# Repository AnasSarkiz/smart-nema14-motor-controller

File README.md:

# Active routing — 0.0.53-alpha.0

Read `docs/REV53-LOGIC-POWER-ESCAPES.md`. The canonical native replay retains
all56/120 complete nets, with240 required opens,128 tracks,82 ordinary0.30/0.45mm
full through vias,five manifested TypeVII thermal vias and seven filled regions.
Native other-errors:0; unchanged strict and filled-copper clearance failures:0;
GND remains one physical network. Original purchased definitions, all165 fitted
model transforms, capacitor placement, motor and carrier are preserved.
The complete USB_VDD bypass/return geometry is screened; V3V3 remains incomplete.
Continue3.3V/core power,PD/eFuse controls,USB pair and ALL remaining physical nets.
Publication is WIP; loaded power/USB/thermal,complete CAM,quote and hardware tests
remain pending. Do not stop at this step. PROTOTYPE FABRICATION READY:NO.

---

# Active routing — 0.0.52-alpha.0

Read `docs/REV52-VM-POWER-ROUTING.md`. Qualified power019 joins56/120 required
nets, including every RAW/protected-VBUS/VM terminal and all prior54 nets.
265 opens,112 tracks,79 ordinary0.30/0.45mm full through vias,five manifested
TypeVII thermal vias,eight native filled regions. Native other-errors:0; strict
and filled-copper clearance failures:0; GND remains one physical network.
Keep all supplier imports/models/placement unchanged. Continue3.3V and core
power,PD/eFuse controls,USB pair with return path,then ALL remaining connections.
Accepted main routes are phase0; VM fanouts phase2; new selected-net routing
is phase3 so existing power copper is a frozen obstacle. Publication is WIP;
loaded power/USB/thermal,complete CAM,assembly quote and hardware tests pending.
Do not stop at this checkpoint. PROTOTYPE FABRICATION READY:NO. No board order.

---

# Smart NEMA 14 Motor Controller

Revision **0.0.53-alpha.0 — WIP prototype** uses **RP2040** and **two USB-C ports**:
`J_USB` supplies motor power through STUSB4500 USB-PD; `J_DATA` connects the
computer's USB data. The board is 35 × 35 mm, four layers, with the original
STEPPERONLINE 14HM11-0404S motor and front carrier. Motor control is open loop.

Configure and read back STUSB4500 NVM for two active sink PDOs: 5 V bootstrap
and preferred 15 V / 1.5 A. Deactivate the factory 20 V PDO. The hardware
interlock combines the 15 V indication, live sink path, MCU request and logic
supervisor. Factory settings alone do not establish a 15 V motor contract.
Computer VBUS only supplies its presence-sense divider; computer power cannot
power the controller or motor. The POWER port must also be connected.

The checked copper connects **56/120 required nets**, including all raw/protected VBUS and all fifteen motor VM terminals: **128 traces, 82 ordinary
0.30 mm drill / 0.45 mm pad through vias, five filled/capped TMC2209 thermal
vias and seven native filled regions**. It has **240 open-port errors**, zero other
native errors and zero independent copper-clearance violations. Routing and
loaded power, USB, thermal and fresh manufacturing qualification continue.
**PROTOTYPE FABRICATION READY: NO. Not hardware tested.**

All 166 electronic references have purpose notes on eleven native A4 sheets;
165 are fitted (R50 is optional). Original official JLCPCB definitions and
OBJ/STEP models are preserved. Actual assembly, model registration and bounded
connector/cable checks pass. See [current routing evidence](docs/REV53-LOGIC-POWER-ESCAPES.md),
[two-port electrical review](docs/REV50-TWO-PORT-ROUTING.md),
[15 V NVM programming](docs/STUSB4500-15V-PROGRAMMING.md), [validation](VALIDATION.md)
and [Cloud task](docs/cloud/TASK.md). The remaining imported TVS schematic
rotation finding is disclosed. Exact-part stock checks are snapshots, not a
customer PCBA allocation or assembly quote.

The lockfile pins Bun 1.3.9, tscircuit 0.0.2757, CLI 0.1.2257, core 0.0.2107,
native Pipeline9 0.0.962 and coherent released dependencies.

```bash
bash scripts/cloud-setup.sh
bash scripts/cloud-smoke.sh
bun run typecheck
bun run build
```

Setup/startup do not route. The intermediate build exits 1 while required opens
remain. Routing uses bounded native Pipeline9 batches and qualified saved source
paths, without supplier edits, generated JSON edits or weaker checks.

Public destinations: [GitHub main](https://github.com/AnasSarkiz/smart-nema14-motor-controller)
and [tscircuit](https://tscircuit.com/AnasSarkiz/smart-nema14-motor-controller--01a0fd9b).
Publication receipts identify exact matching source, Circuit JSON and CAD bytes.
No fabrication order is authorized.

---

## Historical revision 48 record

The following is preserved history. Its one-port architecture, counts, toolchain
and CAD limitations do not describe the current two-port revision.

# Smart NEMA 14 Motor Controller

Revision **0.0.48-alpha.0** — **RP2040 + autonomous STUSB4500 USB-PD**.
**Partially routed prototype. PROTOTYPE FABRICATION READY: NO. Not hardware tested.**

The user-requested redesign replaces STM32/TCPP01 with official RP2040,
external 2 MB QSPI flash, 12 MHz crystal and a dedicated STUSB4500 sink with
back-to-back P-channel power switches. The former MCU had UCPD hardware but
qualified PD firmware was absent; USB-C alone did not establish working PD.
The new controller negotiates autonomously using its factory sink PDOs.
Firmware must qualify the actual contract before enabling the motor/current.

The CAN interface uses a new MCP2515 SPI controller and retains SN65HVD230.
A functional magnetic buzzer driver is added; TMP112 remains the I2C sensor.
Its sheet now includes the sensor, pull-ups, bypasses and buzzer circuit.
All **147 electronic references / 146 default fitted** have purpose notes on
nine native A4 sheets. Only R50, the optional CAN termination link, is DNP.

The board remains **35 x 35 mm, four layers**, with the original four
connectors, front carrier and exact **STEPPERONLINE 14HM11-0404S** single-front-
shaft motor. AS5600 stays removed; motor control is open loop.

See [the complete redesign and every review request](docs/RP2040-USB-PD-REDESIGN.md),
[current routing checkpoint](docs/REV48-ROUTING-CHECKPOINT.md),
[current validation](VALIDATION.md) and [Cloud task](docs/cloud/TASK.md).
Manufacturer pin/BOM and initial placement/model reviews permit routing.
Complete copper, power/USB/thermal/CAM qualification and hardware tests remain.
The full official schematic analyzer leaves one imported TVS rotation defect.
No purchased import, pad mapping, model, DRC or TypeScript rule is patched.

Fresh native [Circuit JSON](dist/index/circuit.json) contains **97 traces,
79 ordinary through vias and8 native ground pours**. **64 of108 required nets** have
one independently measured physical copper island. Native checking still
reports **227 open-port errors**, with zero other native errors and zero strict
copper/drill/edge/keepout violations in this partial build. The build exits1
because connectivity remains incomplete. It is not ready to order.
Old STM32 copper is preserved historically and deliberately cannot be replayed
against the new RP2040 pin selectors. Revision 43 Gerbers/exports cannot
manufacture this revision.

The reproducible lockfile uses Bun1.3.9, tscircuit0.0.2750 / CLI0.1.2254 /
core0.0.2105 / native Pipeline9 0.0.962 with coherent released dependencies.
Frozen installation succeeds through the official registry mirror with normal
TLS/integrity. No substitute router, dependency patch or proxy bypass is used.
Saving a Cloud draft alone does not activate its network policy.

All12 ICs and all146 fitted genuine STEP models pass actual CadQuery import,
solid validity and export/reimport. Current internal placements pass actual mounted146-mesh nominal envelope checks.
The native placement screen retains three orientation suggestions; they remain
explicit alongside the one imported TVS schematic-style finding.
All54 exact part numbers have positive official JLCPCB stock/SMT availability
checked2026-10-07 12:01UTC; customer allocation remains pending. The5-board
fitted-part baseline is$27.261 per board, excluding PCB, assembly/loading fees,
supplier losses, shipping/tax, carrier and motor. This is not a delivered quote.

```bash
bash scripts/cloud-setup.sh
bash scripts/cloud-smoke.sh
bun run build
bun run typecheck
```

Installation/startup do not route. Routing uses one bounded selected-net
native Pipeline9 job at a time on Linux through scripts/run-cloud-routing.py,
plus supported native saved manual paths. All56 current vias measure0.30mm
drill /0.45mm pad and span all four layers. Via-in-pad is disabled. Outer power,
complete loaded widths and USB coupling/return require copper qualification.

The standard JST programmer's five-pin order and protected SWD paths are
preserved. Its VOUT is isolated; independently power the target and use an
RP2040 programming target. The 38 wiring assertions pass; successful flashing
has not been tested.

Public destinations: [GitHub main](https://github.com/AnasSarkiz/smart-nema14-motor-controller)
and [tscircuit](https://tscircuit.com/AnasSarkiz/smart-nema14-motor-controller--01a0fd9b).
Publication receipts identify the exact successfully uploaded revision; a
local version number does not prove publication. The runtime packet includes
unchanged official OBJ/STEP dependencies and matching native JSON, excluding
old experiments. Full historical evidence and the tscircuit skill remain in Git.
No fabrication order is authorized.

The mounted native GLB has an empty J_SWD mesh after intermittent HTTP503
from the standard programmer's original model URL. The mechanical guard
reports145/146 fitted meshes measured, no carrier/fastener/pair collisions
among those145, and **fails** on the missing connector. A successful builder
exit does not qualify complete CAD rendering or fit. Original supplier models
and URLs are retained; no placeholder or changed component is substituted.

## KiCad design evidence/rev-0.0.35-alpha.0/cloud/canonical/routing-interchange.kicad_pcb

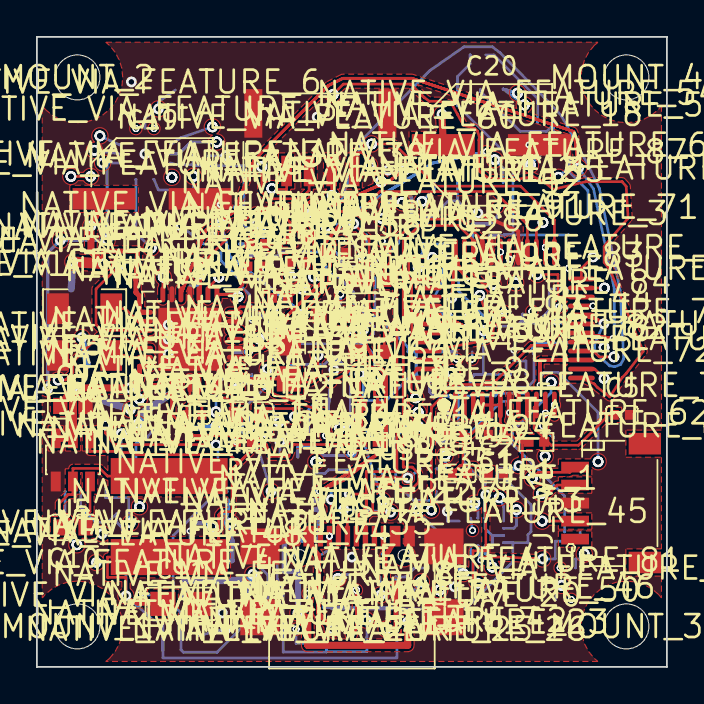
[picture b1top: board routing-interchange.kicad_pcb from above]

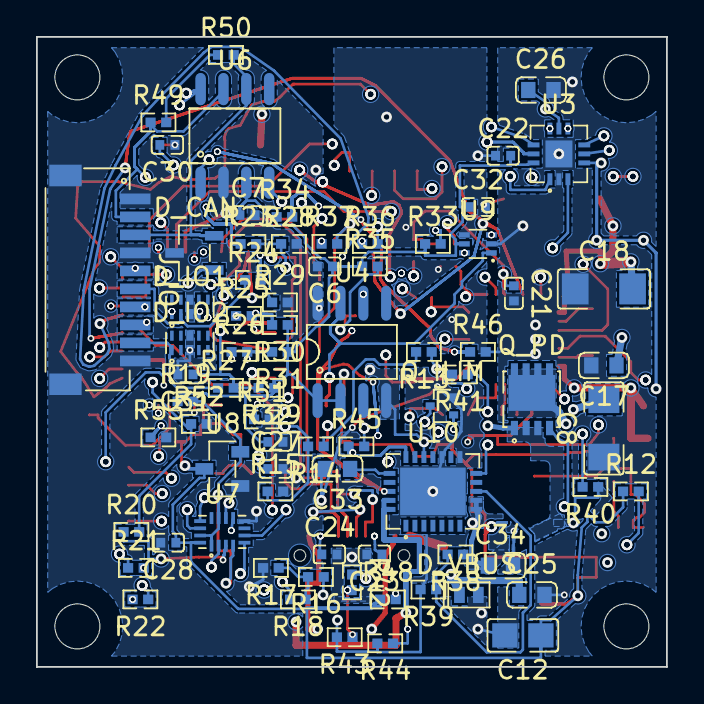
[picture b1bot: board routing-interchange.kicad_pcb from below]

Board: 4 copper layers, 35.0 x 35.0 mm, 213 parts (75 on the bottom side), 82 nets.

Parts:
C1: 100nF; C1
C2: 4.7uF; C2
C3: 100nF; C3
C4: 100nF; C4
C5: 100nF; C5
C6: 100nF; C6
C7: 100nF; C7
C8: 10uF; C8
C9: 100nF; C9
C10: 100nF; C10
C11: 22uF; C11
C12: 22uF; C12
C13: 22nF; C13
C14: 100nF; C14
C15: 4.7uF; C15
C16: 100nF; C16
C17: 100nF; C17
C18: 10uF; C18
C19: 100uF; C19
C20: 100uF; C20
C21: 100nF; C21
C22: 100nF; C22
C23: 330pF; C23
C24: 330pF; C24
C25: 2.2uF; C25
C26: 100nF; C26
C27: 100nF; C27
C28: 100nF; C28
C29: 100nF; C29
C30: 100nF; C30
C31: 100nF; C31
C32: 100nF; C32
C33: 2.2uF; C33
C34: 2.2uF; C34
D_CAN: SM712.TCT; D_CAN
D_IO1: TPD4E05U06DQAR; D_IO1
D_IO2: TPD4E05U06DQAR; D_IO2
D_USB: TPD2EUSB30ADRTR; D_USB
D_VBUS: ESDA25P35-1U1M; D_VBUS
J_IO: SM10B-SRSS-TB(LF)(SN); J_IO
J_MOTOR: SM04B-GHS-TB(LF)(SN); J_MOTOR
J_SWD: J_SWD
J_USB: USB4110-GF-A; J_USB
L1: 3.9µH; L1
LED_FAULT: XL-1608SYGC-06; LED_FAULT
LED_POWER: XL-1608SYGC-06; LED_POWER
LED_STATUS: XL-1608SYGC-06; LED_STATUS
MOUNT_1, MOUNT_2, MOUNT_3, MOUNT_4: hole_circle_holeDiameter2.5mm
NATIVE_VIA_FEATURE_1: NATIVE_VIA_FEATURE_1
NATIVE_VIA_FEATURE_2: NATIVE_VIA_FEATURE_2
NATIVE_VIA_FEATURE_3: NATIVE_VIA_FEATURE_3
NATIVE_VIA_FEATURE_4: NATIVE_VIA_FEATURE_4
NATIVE_VIA_FEATURE_5: NATIVE_VIA_FEATURE_5
NATIVE_VIA_FEATURE_6: NATIVE_VIA_FEATURE_6
NATIVE_VIA_FEATURE_7: NATIVE_VIA_FEATURE_7
NATIVE_VIA_FEATURE_8: NATIVE_VIA_FEATURE_8
NATIVE_VIA_FEATURE_9: NATIVE_VIA_FEATURE_9
NATIVE_VIA_FEATURE_10: NATIVE_VIA_FEATURE_10
NATIVE_VIA_FEATURE_11: NATIVE_VIA_FEATURE_11
NATIVE_VIA_FEATURE_12: NATIVE_VIA_FEATURE_12
NATIVE_VIA_FEATURE_13: NATIVE_VIA_FEATURE_13
NATIVE_VIA_FEATURE_14: NATIVE_VIA_FEATURE_14
NATIVE_VIA_FEATURE_15: NATIVE_VIA_FEATURE_15
NATIVE_VIA_FEATURE_16: NATIVE_VIA_FEATURE_16
NATIVE_VIA_FEATURE_17: NATIVE_VIA_FEATURE_17
NATIVE_VIA_FEATURE_18: NATIVE_VIA_FEATURE_18
NATIVE_VIA_FEATURE_19: NATIVE_VIA_FEATURE_19
NATIVE_VIA_FEATURE_20: NATIVE_VIA_FEATURE_20
NATIVE_VIA_FEATURE_21: NATIVE_VIA_FEATURE_21
NATIVE_VIA_FEATURE_22: NATIVE_VIA_FEATURE_22
NATIVE_VIA_FEATURE_23: NATIVE_VIA_FEATURE_23
NATIVE_VIA_FEATURE_24: NATIVE_VIA_FEATURE_24
NATIVE_VIA_FEATURE_25: NATIVE_VIA_FEATURE_25
NATIVE_VIA_FEATURE_26: NATIVE_VIA_FEATURE_26
NATIVE_VIA_FEATURE_27: NATIVE_VIA_FEATURE_27
NATIVE_VIA_FEATURE_28: NATIVE_VIA_FEATURE_28
NATIVE_VIA_FEATURE_29: NATIVE_VIA_FEATURE_29
NATIVE_VIA_FEATURE_30: NATIVE_VIA_FEATURE_30
NATIVE_VIA_FEATURE_31: NATIVE_VIA_FEATURE_31
NATIVE_VIA_FEATURE_32: NATIVE_VIA_FEATURE_32
NATIVE_VIA_FEATURE_33: NATIVE_VIA_FEATURE_33
NATIVE_VIA_FEATURE_34: NATIVE_VIA_FEATURE_34
NATIVE_VIA_FEATURE_35: NATIVE_VIA_FEATURE_35
NATIVE_VIA_FEATURE_36: NATIVE_VIA_FEATURE_36
NATIVE_VIA_FEATURE_37: NATIVE_VIA_FEATURE_37
NATIVE_VIA_FEATURE_38: NATIVE_VIA_FEATURE_38
NATIVE_VIA_FEATURE_39: NATIVE_VIA_FEATURE_39
NATIVE_VIA_FEATURE_40: NATIVE_VIA_FEATURE_40
NATIVE_VIA_FEATURE_41: NATIVE_VIA_FEATURE_41
NATIVE_VIA_FEATURE_42: NATIVE_VIA_FEATURE_42
NATIVE_VIA_FEATURE_43: NATIVE_VIA_FEATURE_43
NATIVE_VIA_FEATURE_44: NATIVE_VIA_FEATURE_44
NATIVE_VIA_FEATURE_45: NATIVE_VIA_FEATURE_45
NATIVE_VIA_FEATURE_46: NATIVE_VIA_FEATURE_46
NATIVE_VIA_FEATURE_47: NATIVE_VIA_FEATURE_47
NATIVE_VIA_FEATURE_48: NATIVE_VIA_FEATURE_48
NATIVE_VIA_FEATURE_49: NATIVE_VIA_FEATURE_49
NATIVE_VIA_FEATURE_50: NATIVE_VIA_FEATURE_50
NATIVE_VIA_FEATURE_51: NATIVE_VIA_FEATURE_51
NATIVE_VIA_FEATURE_52: NATIVE_VIA_FEATURE_52
NATIVE_VIA_FEATURE_53: NATIVE_VIA_FEATURE_53
NATIVE_VIA_FEATURE_54: NATIVE_VIA_FEATURE_54
NATIVE_VIA_FEATURE_55: NATIVE_VIA_FEATURE_55
NATIVE_VIA_FEATURE_56: NATIVE_VIA_FEATURE_56
NATIVE_VIA_FEATURE_57: NATIVE_VIA_FEATURE_57
NATIVE_VIA_FEATURE_58: NATIVE_VIA_FEATURE_58
NATIVE_VIA_FEATURE_59: NATIVE_VIA_FEATURE_59
NATIVE_VIA_FEATURE_60: NATIVE_VIA_FEATURE_60
NATIVE_VIA_FEATURE_61: NATIVE_VIA_FEATURE_61
NATIVE_VIA_FEATURE_62: NATIVE_VIA_FEATURE_62
NATIVE_VIA_FEATURE_63: NATIVE_VIA_FEATURE_63
NATIVE_VIA_FEATURE_64: NATIVE_VIA_FEATURE_64
NATIVE_VIA_FEATURE_65: NATIVE_VIA_FEATURE_65
NATIVE_VIA_FEATURE_66: NATIVE_VIA_FEATURE_66
NATIVE_VIA_FEATURE_67: NATIVE_VIA_FEATURE_67
NATIVE_VIA_FEATURE_68: NATIVE_VIA_FEATURE_68
NATIVE_VIA_FEATURE_69: NATIVE_VIA_FEATURE_69
NATIVE_VIA_FEATURE_70: NATIVE_VIA_FEATURE_70
NATIVE_VIA_FEATURE_71: NATIVE_VIA_FEATURE_71
NATIVE_VIA_FEATURE_72: NATIVE_VIA_FEATURE_72
NATIVE_VIA_FEATURE_73: NATIVE_VIA_FEATURE_73
NATIVE_VIA_FEATURE_74: NATIVE_VIA_FEATURE_74
NATIVE_VIA_FEATURE_75: NATIVE_VIA_FEATURE_75
NATIVE_VIA_FEATURE_76: NATIVE_VIA_FEATURE_76
NATIVE_VIA_FEATURE_77: NATIVE_VIA_FEATURE_77
NATIVE_VIA_FEATURE_78: NATIVE_VIA_FEATURE_78
NATIVE_VIA_FEATURE_79: NATIVE_VIA_FEATURE_79
NATIVE_VIA_FEATURE_80: NATIVE_VIA_FEATURE_80
NATIVE_VIA_FEATURE_81: NATIVE_VIA_FEATURE_81
NATIVE_VIA_FEATURE_82: NATIVE_VIA_FEATURE_82
NATIVE_VIA_FEATURE_83: NATIVE_VIA_FEATURE_83
NATIVE_VIA_FEATURE_84: NATIVE_VIA_FEATURE_84
NATIVE_VIA_FEATURE_85: NATIVE_VIA_FEATURE_85
NATIVE_VIA_FEATURE_86: NATIVE_VIA_FEATURE_86
NATIVE_VIA_FEATURE_87: NATIVE_VIA_FEATURE_87
NATIVE_VIA_FEATURE_88: NATIVE_VIA_FEATURE_88
NATIVE_VIA_FEATURE_89: NATIVE_VIA_FEATURE_89
NATIVE_VIA_FEATURE_90: NATIVE_VIA_FEATURE_90
NATIVE_VIA_FEATURE_91: NATIVE_VIA_FEATURE_91
NATIVE_VIA_FEATURE_92: NATIVE_VIA_FEATURE_92
NATIVE_VIA_FEATURE_93: NATIVE_VIA_FEATURE_93
NATIVE_VIA_FEATURE_94: NATIVE_VIA_FEATURE_94
NATIVE_VIA_FEATURE_95: NATIVE_VIA_FEATURE_95
NATIVE_VIA_FEATURE_96: NATIVE_VIA_FEATURE_96
NATIVE_VIA_FEATURE_97: NATIVE_VIA_FEATURE_97
NATIVE_VIA_FEATURE_98: NATIVE_VIA_FEATURE_98
Q_ILIM: DMG1012T-7; Q_ILIM
Q_PD: STL11N3LLH6; Q_PD
R1: 10kΩ; R1
R2: 4.7kΩ; R2
R3: 4.7kΩ; R3
R4: 1kΩ; R4
R5: 1Ω; R5
R6: 1Ω; R6
R7: 10kΩ; R7
R8: 10kΩ; R8
R9: 10kΩ; R9
R10: 10kΩ; R10
R11: 10kΩ; R11
R12: 10kΩ; R12
R13: 100kΩ; R13
R14: 1kΩ; R14
R15: 6.04kΩ; R15
R16: 220kΩ; R16
R17: 10kΩ; R17
R18: 1kΩ; R18
R19: 10kΩ; R19
R20: 1kΩ; R20
R21: 1kΩ; R21
R22: 1kΩ; R22
R23: 1kΩ; R23
R24: 1kΩ; R24
R25: 1kΩ; R25
R26: 1kΩ; R26
R27: 1kΩ; R27
R28: 10kΩ; R28
R29: 10kΩ; R29
R30: 10kΩ; R30
R31: 10kΩ; R31
R32: 10kΩ; R32
R33: 10kΩ; R33
R34: 10kΩ; R34
R35: 1kΩ; R35
R36: 1kΩ; R36
R37: 1kΩ; R37
R38: 100kΩ; R38
R39: 47kΩ; R39
R40: 100kΩ; R40
R41: 1kΩ; R41
R42: 4.7kΩ; R42
R43: 6.04kΩ; R43
R44: 24kΩ; R44
R45: 24kΩ; R45
R46: 10kΩ; R46
R48: 10kΩ; R48
R49: 120Ω; R49
R50: 0Ω; R50
R51: 100kΩ; R51
R52: 100kΩ; R52
R53: 100kΩ; R53
U1: STM32G0B1CBT6; U1
U2: TMC2209-LA; U2
U3: TCPP01-M12; U3
U4: AS5600-ASOM; U4
U5: AP63203WU-7; U5
U6: SN65HVD230DR; U6
U7: TMUX1511RSVR; U7
U8: TLV803EA30DBZR; U8
U9: TMP112AIDRLR; U9
U10: TPS26600RHFR; U10

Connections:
BUCK_BST: C10.1, U5.6
BUCK_SW: C10.2, L1.1, U5.5
CAN_H: D_CAN.1, J_IO.2, R49.1, U6.7
CAN_L: D_CAN.2, J_IO.3, R50.2, U6.6
CAN_RS: R34.2, U1.42, U6.8
CAN_RX: U1.44, U6.4
CAN_TERM_LINK: R49.2, R50.1
CAN_TX: U1.45, U6.1
EFUSE_DVDT: C33.1, U10.20
EFUSE_EN: R38.2, R39.1, U10.10
EFUSE_FLT_N: R48.2, U1.43, U10.22
EFUSE_ILIM: R44.1, R45.1, U10.19
EFUSE_ILIM_SWITCH: Q_ILIM.3, R45.2
EFUSE_OVP: R42.2, R43.1, U10.12
EFUSE_OVP_TOP_1: R40.2, R41.1
EFUSE_OVP_TOP_2: R41.2, R42.1
EFUSE_RTN: C33.2, Q_ILIM.2, R39.2, R43.2, R44.2, U10.13, U10.15, U10.25
EXT_DIR: R24.2, R29.1, U1.20
EXT_DIR_CONN: D_IO1.2, J_IO.6, R24.1
EXT_ENABLE_N: R25.2, R30.2, U1.21
EXT_ENABLE_N_CONN: D_IO1.4, J_IO.7, R25.1
EXT_STEP: R23.2, R28.1, U1.19
EXT_STEP_CONN: D_IO1.1, J_IO.5, R23.1
GND: C1.2, C2.2, C3.2, C4.2, C5.2, C6.2, C7.2, C8.2, C9.2, C11.2, C12.2, C15.2, C16.2, C17.2, C18.2, C19.2, C20.2, C21.2, C22.2, C23.2, C24.2, C25.2, C26.2, C27.2, C28.2, C29.2, C30.2, C31.2, C32.2, C34.2, D_CAN.3, D_IO1.3, D_IO1.8, D_IO2.3, D_IO2.8, D_USB.3, D_VBUS.2, J_IO.1, J_IO.4, J_IO.10, J_IO.11, J_IO.12, J_MOTOR.5, J_MOTOR.6, J_SWD.3, J_USB.8, J_USB.9, J_USB.10, J_USB.11, J_USB.22, J_USB.23, LED_FAULT.1, LED_POWER.1, LED_STATUS.1, R5.2, R6.2, R8.2, R9.2, R11.2, R15.2, R17.2, R28.2, R29.2, R46.2, R51.2, R52.2, R53.2, U1.7, U1.29, U1.32, U2.3, U2.7, U2.9, U2.10, U2.13, U2.18, U2.20, U2.25, U2.29, U3.2, U3.13, U4.4, U4.8, U5.4, U6.2, U7.8, U8.1, U9.2, U9.4, U10.17
I2C_SCL: R2.2, U1.47, U4.7, U9.1
I2C_SDA: R3.2, U1.48, U4.6, U9.6
LED_FAULT_A: LED_FAULT.2, R37.2
LED_FAULT_DRIVE: R37.1, U1.31
LED_POWER_A: LED_POWER.2, R35.2
LED_STATUS_A: LED_STATUS.2, R36.2
LED_STATUS_DRIVE: R36.1, U1.30
LIMIT1: C30.1, R26.2, R31.2, U1.22
LIMIT1_CONN: D_IO1.5, J_IO.8, R26.1
LIMIT2: C31.1, R27.2, R32.2, U1.23
LIMIT2_CONN: D_IO2.1, J_IO.9, R27.1
MOTOR_A1: J_MOTOR.1, U2.24
MOTOR_A2: J_MOTOR.2, U2.21
MOTOR_B1: J_MOTOR.3, U2.26
MOTOR_B2: J_MOTOR.4, U2.1
NRST: C5.1, R1.2, R22.2, U1.10
NRST_CONN: J_SWD.5, U7.10
NRST_GUARDED: R22.1, U7.9
PD_CC1_CONN: C23.1, J_USB.18, U3.7
PD_CC1_MCU: U1.28, U3.3
PD_CC2_CONN: C24.1, J_USB.15, U3.9
PD_CC2_MCU: U1.27, U3.1
PD_DB: U1.24, U3.10
PD_FLT: R12.2, U1.25, U3.11
PD_GATE: Q_PD.4, U3.5
PD_OVP: R14.2, R15.1, U3.6
PD_OVP_SERIES: R13.2, R14.1
POWER_GOOD: R19.2, U7.1, U7.4, U7.11, U7.15, U8.2
POWER_HIGH_CURRENT: Q_ILIM.1, R46.1, U1.26
SWCLK: R21.2, R53.1, U1.36
SWCLK_CONN: J_SWD.4, U7.5
SWCLK_GUARDED: R21.1, U7.6
SWDIO: R20.2, R52.1, U1.35
SWDIO_CONN: J_SWD.2, U7.2
SWDIO_GUARDED: R20.1, U7.3
TEMP_ALERT_N: R33.2, U1.12, U9.3
TMC_5VOUT: C15.1, R10.1, U2.8
TMC_CPI: C13.2, U2.5
TMC_CPO: C13.1, U2.4
TMC_DIAG: U1.16, U2.11
TMC_DIR: R9.1, U1.18, U2.19
TMC_ENABLE_N: R7.2, U1.15, U2.2
TMC_SENSE_A: R5.1, U2.23
TMC_SENSE_B: R6.1, U2.27
TMC_STEP: R8.1, U1.17, U2.16
TMC_UART_RX: R4.2, U1.14, U2.14
TMC_UART_TX: R4.1, U1.13
TMC_VCP: C14.1, U2.6
TMC_VREF: C21.1, R10.2, R11.1, U2.17
USB_DM: D_USB.2, J_USB.12, J_USB.17, U1.33
USB_DP: D_USB.1, J_USB.13, J_USB.16, U1.34
V3V3: C1.1, C2.1, C3.1, C4.1, C6.1, C7.1, C11.1, C12.1, C16.1, C22.1, C28.1, C29.1, C32.1, L1.2, R1.1, R2.1, R3.1, R7.1, R12.1, R19.1, R30.1, R31.1, R32.1, R33.1, R34.1, R35.1, R48.1, U1.4, U1.5, U1.6, U2.15, U3.12, U4.1, U4.2, U5.1, U6.3, U7.16, U8.3, U9.5
VBUS_ADC: C27.1, R51.1, U1.11, U7.13
VBUS_ADC_PRE_GUARD: R18.2, U7.14
VBUS_CONN: C25.1, C26.1, D_VBUS.1, J_USB.20, J_USB.21, Q_PD.5, Q_PD.6, Q_PD.7, Q_PD.8, Q_PD.9, R13.1, U3.8
VBUS_DIV: R16.2, R17.1, R18.1
VBUS_PROTECTED: C34.1, Q_PD.1, Q_PD.2, Q_PD.3, R16.1, R38.1, R40.1, U3.4, U10.8, U10.9
VM: C8.1, C9.1, C14.2, C17.1, C18.1, C19.1, C20.1, U2.22, U2.28, U5.2, U5.3, U10.23, U10.24

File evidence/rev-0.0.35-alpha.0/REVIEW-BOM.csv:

reference,manufacturer_part_number,jlcpcb_part_number,resistance_ohms,capacitance_f,inductance_h,fit_default,optional_reason
"C1","CL05B104KO5NNNC","C1525","","1e-7","","true",""
"C2","CL05A475MP5NRNC","C23733","","0.0000047","","true",""
"C3","CL05B104KO5NNNC","C1525","","1e-7","","true",""
"C4","CL05B104KO5NNNC","C1525","","1e-7","","true",""
"C5","CL05B104KO5NNNC","C1525","","1e-7","","true",""
"C6","CL05B104KO5NNNC","C1525","","1e-7","","false","Supply bypass for optional U4; omit with encoder"
"C7","CL05B104KO5NNNC","C1525","","1e-7","","true",""
"C8","CL31A106KBHNNNE","C13585","","0.00001","","true",""
"C9","CC0603KRX7R9BB104","C14663","","1e-7","","true",""
"C10","CC0603KRX7R9BB104","C14663","","1e-7","","true",""
"C11","CL21A226MAQNNNE","C45783","","0.000022","","true",""
"C12","CL21A226MAQNNNE","C45783","","0.000022","","true",""
"C13","CL05B223KB5VPNC","C307335","","2.2e-8","","true",""
"C14","CC0603KRX7R9BB104","C14663","","1e-7","","true",""
"C15","CL21A475KBQNNNE","C98192","","0.0000047","","true",""
"C16","CL05B104KO5NNNC","C1525","","1e-7","","true",""
"C17","CC0603KRX7R9BB104","C14663","","1e-7","","true",""
"C18","CL31A106KBHNNNE","C13585","","0.00001","","true",""
"C19","EEEFPV101XAP","C178585","","0.0001","","true",""
"C20","EEEFPV101XAP","C178585","","0.0001","","true",""
"C21","CL05B104KO5NNNC","C1525","","1e-7","","true",""
"C22","CL05B104KO5NNNC","C1525","","1e-7","","true",""
"C23","TCC0402COG331J500AT","C5448795","","3.3e-10","","true",""
"C24","TCC0402COG331J500AT","C5448795","","3.3e-10","","true",""
"C25","UMK107BBJ225KA-T","C268016","","0.0000022","","true",""
"C26","CC0603KRX7R9BB104","C14663","","1e-7","","true",""
"C27","CL05B104KO5NNNC","C1525","","1e-7","","true",""
"C28","CL05B104KO5NNNC","C1525","","1e-7","","true",""
"C29","CL05B104KO5NNNC","C1525","","1e-7","","true",""
"C30","CL05B104KO5NNNC","C1525","","1e-7","","true",""
"C31","CL05B104KO5NNNC","C1525","","1e-7","","true",""
"C32","CL05B104KO5NNNC","C1525","","1e-7","","true",""
"C33","UMK107BBJ225KA-T","C268016","","0.0000022","","true",""
"C34","UMK107BBJ225KA-T","C268016","","0.0000022","","true",""
"D_CAN","SM712.TCT","C12067","","","","true",""
"D_IO1","TPD4E05U06DQAR","C138714","","","","true",""
"D_IO2","TPD4E05U06DQAR","C138714","","","","true",""
"D_USB","TPD2EUSB30ADRTR","C94934","","","","true",""
"D_VBUS","ESDA25P35-1U1M","C1974707","","","","true",""
"J_IO","SM10B-SRSS-TB(LF)(SN)","C160409","","","","true",""
"J_MOTOR","SM04B-GHS-TB(LF)(SN)","C189895","","","","true",""
"J_SWD","SM05B-SRSS-TB(LF)(SN)","C136657","","","","true",""
"J_USB","USB4110-GF-A","C5143397","","","","true",""
"L1","SRN6028C-3R9M","C19947652","","","3.9uH","true",""
"LED_FAULT","XL-1608SYGC-06","C965805","","","","true",""
"LED_POWER","XL-1608SYGC-06","C965805","","","","true",""
"LED_STATUS","XL-1608SYGC-06","C965805","","","","true",""
"Q_ILIM","DMG1012T-7","C20512","","","","true",""
"Q_PD","STL11N3LLH6","C2965326","","","","true",""
"R1","0402WGF1002TCE","C25744","10000","","","true",""
"R2","0402WGF4701TCE","C25900","4700","","","true",""
"R3","0402WGF4701TCE","C25900","4700","","","true",""
"R4","0402WGF1001TCE","C11702","1000","","","true",""
"R5","RT1206BRD071RL","C513714","1","","","true",""
"R6","RT1206BRD071RL","C513714","1","","","true",""
"R7","0402WGF1002TCE","C25744","10000","","","true",""
"R8","0402WGF1002TCE","C25744","10000","","","true",""
"R9","0402WGF1002TCE","C25744","10000","","","true",""
"R10","0402WGF1002TCE","C25744","10000","","","true",""
"R11","0402WGF1002TCE","C25744","10000","","","true",""
"R12","0402WGF1002TCE","C25744","10000","","","true",""
"R13","RT0402BRD07100KL","C852472","100000","","","true",""
"R14","0402WGF1001TCE","C11702","1000","","","true",""
"R15","RT0402BRD076K04L","C852895","6040","","","true",""
"R16","0402WGF2203TCE","C25767","220000","","","true",""
"R17","0402WGF1002TCE","C25744","10000","","","true",""
"R18","0402WGF1001TCE","C11702","1000","","","true",""
"R19","0402WGF1002TCE","C25744","10000","","","true",""
"R20","0402WGF1001TCE","C11702","1000","","","true",""
"R21","0402WGF1001TCE","C11702","1000","","","true",""
"R22","0402WGF1001TCE","C11702","1000","","","true",""
"R23","0402WGF1001TCE","C11702","1000","","","true",""
"R24","0402WGF1001TCE","C11702","1000","","","true",""
"R25","0402WGF1001TCE","C11702","1000","","","true",""
"R26","0402WGF1001TCE","C11702","1000","","","true",""
"R27","0402WGF1001TCE","C11702","1000","","","true",""
"R28","0402WGF1002TCE","C25744","10000","","","true",""
"R29","0402WGF1002TCE","C25744","10000","","","true",""
"R30","0402WGF1002TCE","C25744","10000","","","true",""
"R31","0402WGF1002TCE","C25744","10000","","","true",""
"R32","0402WGF1002TCE","C25744","10000","","","true",""
"R33","0402WGF1002TCE","C25744","10000","","","true",""
"R34","0402WGF1002TCE","C25744","10000","","","true",""
"R35","0402WGF1001TCE","C11702","1000","","","true",""
"R36","0402WGF1001TCE","C11702","1000","","","true",""
"R37","0402WGF1001TCE","C11702","1000","","","true",""
"R38","RT0402BRD07100KL","C852472","100000","","","true",""
"R39","0402WGF4702TCE","C25792","47000","","","true",""
"R40","RT0402BRD07100KL","C852472","100000","","","true",""
"R41","0402WGF1001TCE","C11702","1000","","","true",""
"R42","0402WGF4701TCE","C25900","4700","","","true",""
"R43","RT0402BRD076K04L","C852895","6040","","","true",""
"R44","0402WGF2402TCE","C25769","24000","","","true",""
"R45","0402WGF2402TCE","C25769","24000","","","true",""
"R46","0402WGF1002TCE","C25744","10000","","","true",""
"R48","0402WGF1002TCE","C25744","10000","","","true",""
"R49","0402WGF1200TCE","C25079","120","","","true",""
"R50","0402WGF0000TCE","C17168","0","","","false","CAN termination link: omit except on bus endpoints"
"R51","RT0402BRD07100KL","C852472","100000","","","true",""
"R52","RT0402BRD07100KL","C852472","100000","","","true",""
"R53","RT0402BRD07100KL","C852472","100000","","","true",""
"U1","STM32G0B1CBT6","C2847904","","","","true",""
"U2","TMC2209-LA","C465949","","","","true",""
"U3","TCPP01-M12","C1121848","","","","true",""
"U4","AS5600-ASOM","C79815","","","","false","Default open-loop assembly: selected motor has no rear shaft for AS5600 magnet"
"U5","AP63203WU-7","C780769","","","","true",""
"U6","SN65HVD230DR","C12084","","","","true",""
"U7","TMUX1511RSVR","C2673275","","","","true",""
"U8","TLV803EA30DBZR","C5218924","","","","true",""
"U9","TMP112AIDRLR","C28927","","","","true",""
"U10","TPS26600RHFR","C2155767","","","","true",""

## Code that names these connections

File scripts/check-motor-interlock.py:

"""Independent source-pin truth and manufacturer electrical-corner review.

Datasheet limits are recorded with their actual temperature/voltage scope.
This check does not simulate silicon or invent physical startup measurements.
"""
import hashlib
import itertools
import json
from pathlib import Path
import sys

circuit_path, report_path = map(Path, sys.argv[1:3])
circuit_bytes = circuit_path.read_bytes()
circuit = json.loads(circuit_bytes)
components = {row['name']: row for row in circuit if row['type'] == 'source_component'}
nets = {row['source_net_id']: row['name'] for row in circuit if row['type'] == 'source_net'}
ports = [row for row in circuit if row['type'] == 'source_port']
traces = [row for row in circuit if row['type'] == 'source_trace']


def pin_net(reference, number):
    owner = components[reference]['source_component_id']
    port = next(row for row in ports if row['source_component_id'] == owner and row['pin_number'] == number)
    names = {nets[net] for trace in traces if port['source_port_id'] in trace['connected_source_port_ids'] for net in trace['connected_source_net_ids']}
    assert len(names) == 1, (reference, number, names)
    return names.pop()


assert pin_net('U2', 15) == pin_net('R7', 1) == pin_net('U_MOTOR_ENN', 5) == 'V3V3'
assert pin_net('U2', 2) == pin_net('R7', 2) == pin_net('U_MOTOR_ENN', 4) == 'TMC_ENABLE_N'
assert components['U_MOTOR_ENN']['supplier_part_numbers']['jlcpcb'] == ['C485081']
for pin, expected in {1: 'GND', 2: 'GND', 3: 'MOTOR_ENABLE_DRIVE', 6: 'MOTOR_POWER_GOOD'}.items():
    assert pin_net('U_MOTOR_ENN', pin) == expected
assert pin_net('U_MOTOR_SUPERVISOR', 2) == 'MOTOR_POWER_GOOD'
assert pin_net('D_PD_VALID', 1) == 'PD_LOAD_ENABLE_N'  # purchased cathode
assert pin_net('D_PD_VALID', 2) == 'PD_PATH_INVALID_N'  # purchased anode
assert components['D_PD_VALID']['supplier_part_numbers']['jlcpcb'] == ['C668868']
assert not {'Q_MOTOR_ENABLE', 'Q_MOTOR_POWER_GOOD', 'R_MOTOR_GATE_SERIES', 'R_MOTOR_GATE_OFF'} & components.keys()
assert components['R7']['resistance'] == 10000
assert components['R_MOTOR_BOOT_PULLUP']['resistance'] == 180000

# Independent TI SCES417L eight-row multiplexer-inverting truth table, not
# inferred from this design's intended NAND name. IN1 is physically tied low.
gate98_table = {(0, 0, 0): 1, (0, 0, 1): 1, (0, 1, 0): 0, (0, 1, 1): 0,
                (1, 0, 0): 1, (1, 0, 1): 0, (1, 1, 0): 1, (1, 1, 1): 0}
truth_rows = []
for request_n, contract_n, path_invalid_n, power_good in itertools.product((0, 1), repeat=4):
    nor_output = int(not (request_n or contract_n or path_invalid_n))
    enn = gate98_table[(power_good, 0, nor_output)]
    permitted = request_n == contract_n == path_invalid_n == 0 and power_good == 1
    assert (enn == 0) == permitted
    truth_rows.append(dict(request_n=request_n, contract_15_n=contract_n, path_invalid_n=path_invalid_n, power_good=power_good, enn=enn))

reset_load_ua = 1.7 / (180000 * 0.99) * 1e6 + 5
power_good_high_at_3v = 3.0 - 5e-6 * 180000 * 1.01
diode_shift_low_at_25c = 0.4 + 0.32
assert reset_load_ua < 15  # TI POR VOL guarantee load, including negative input leakage
assert power_good_high_at_3v > 1.87  # gate98 VT+ max at VCC=3V
assert 0.3 < 0.35  # POR low versus gate98 VT- min at VCC=1.65V
assert diode_shift_low_at_25c < 0.84  # Schmitt VT- min at VCC=3V
enn_sink_ma = 3.36 / (10000 * 0.99) * 1000 + 0.010
assert enn_sink_ma < 16 and 0.45 < 0.3 * 3.0
assert 2.1 > 1.65 > 0.7  # TMC minimum rising reset > logic min > supervisor POR max

scenarios = [
    dict(name='data only / no logic supply', logic_powered=False, motor_powered=False, motor_enabled=False),
    dict(name='PD5V, with or without data', inputs=[0, 1, 0, 1], enn=1),
    dict(name='PD15V, no request', inputs=[1, 0, 0, 1], enn=1),
    dict(name='PD15V, qualified request', inputs=[0, 0, 0, 1], enn=0),
    dict(name='detach with stale POWER_OK2 and held-up logic', inputs=[0, 0, 1, 1], enn=1),
    dict(name='renegotiation/path loss', inputs=[0, 0, 1, 1], enn=1),
    dict(name='supervisor reset/brownout, any flags', inputs=[0, 0, 0, 0], enn=1),
    dict(name='factory20V configuration', nvm_acceptance=False, fabrication_configuration_acceptance=False),
]
report = dict(circuit_sha256=hashlib.sha256(circuit_bytes).hexdigest(), chosen_gate='TI SN74LVC1G98DCKR C485081, Schmitt-input NAND configuration',
              passed_pin_truth_and_scoped_static_corners=True, truth_rows=truth_rows, scenarios=scenarios,
              corners=dict(supervisor_max_sink_ua=reset_load_ua, supervisor_guarantee_ua=15, power_good_min_high_at_3v=power_good_high_at_3v,
                           pd_diode_shift_max_low_at_25c=diode_shift_low_at_25c, pd_schmitt_low_limit_at_3v=0.84, enn_max_sink_ma=enn_sink_ma,
                           enn_gate_max_low_at_3v=0.45, tmc_low_limit_at_3v=0.9),
              startup_conclusion='No MOS threshold assumption remains. Supervisor feeds a Schmitt input; rising sub-POR is below the TMC minimum I/O reset-release voltage. ENN and VCC_IO share one rail.',
              limitations=['ST open-drain VOL and BAT54 VF/leakage limits used here are guaranteed at25C; hot/cold diode-shift margins require physical qualification.',
                           'Below1.65V logic behavior is outside its operating range. No measured falling-ramp reset threshold or full-ramp waveform is claimed.',
                           'NVM cold readback, live15V negotiation, exact routed input capacitance/edge checks, detach timing and backfeed measurements remain pending.'],
              physical_startup_tested=False, fabrication_ready=False)
report_path.write_text(json.dumps(report, indent=2) + '\n')
print('16 manufacturer truth combinations and scoped static electrical corners pass; physical startup/PD tests remain pending.')
